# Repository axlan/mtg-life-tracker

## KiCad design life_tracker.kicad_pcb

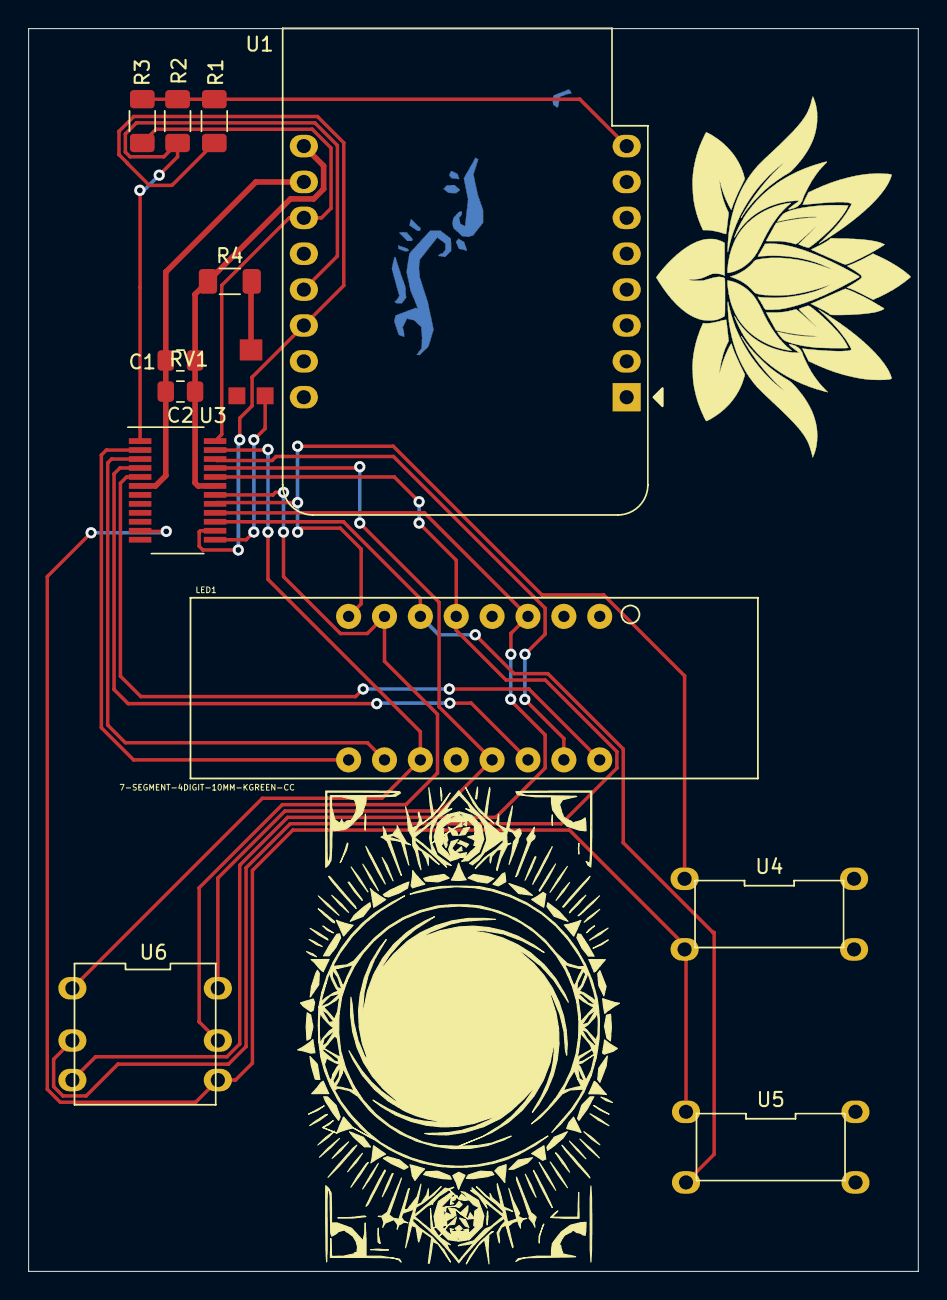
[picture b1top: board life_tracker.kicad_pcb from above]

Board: 2 copper layers, 63.0 x 88.0 mm, 16 parts (1 on the bottom side), 21 nets.

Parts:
C1: 10uF; C_0805_2012Metric_Pad1.18x1.45mm_HandSolder
C2: 0.1uF; C_0805_2012Metric_Pad1.18x1.45mm_HandSolder
LED1: 7-SEGMENT-4DIGIT-10MM-KGREEN-CC; 7-SEGMENT-4DIGIT-YOUNGSUN
R1, R2, R3, R4: 4.7k; R_1206_3216Metric_Pad1.30x1.75mm_HandSolder
RV1: 100k; TC33-SMD-Trimpot
U1: WeMos_D1_mini; WEMOS_D1_mini_light
U3: AS1115-BSST; QSOP-24_3.9x8.7mm_P0.635mm
U4, U5: PTS526-tactile-button; TACTILE-DIP-BUTTON
U6: TACTILE-NAV-STICK-DIP
svg2mod: G***; squirrel2
svg2mod#2: G***; lotus
svg2mod#3: G***; plains_walker_back_simp2

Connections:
+5V: C1.1, C2.1, R4.1, U1.9, U3.19
GND: C1.2, C2.2, U1.10, U3.6
unnamed: LED1.1, U3.2
unnamed: LED1.2, U3.3
unnamed: LED1.3, U3.23, U6.1
unnamed: LED1.5, U3.21, U6.6
unnamed: LED1.6, U3.4
unnamed: LED1.7, U3.22
unnamed: LED1.8, U3.5
unnamed: LED1.11, U3.16, U6.3
unnamed: LED1.13, U3.20, U6.2
unnamed: LED1.14, U3.15, U5.3
unnamed: LED1.15, U3.18, U6.5
unnamed: LED1.16, U3.17, U4.1
unnamed: R1.1, R2.1, R3.1, U1.8
unnamed: R1.2, U1.14, U3.14
unnamed: R2.2, U1.13, U3.1
unnamed: R3.2, U1.11, U3.24
unnamed: R4.2, RV1.2
unnamed: RV1.3, U3.13
unnamed: U3.11, U4.3, U5.1, U6.4

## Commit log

2021-10-16 initial test
2021-10-16 fix symbol directory
2021-10-16 remove unneeded file
2021-10-18 Initial pass at schematic.
2021-10-18 started routing PCB, need to flip D1
2021-10-20 Finished second revision.
2021-10-21 Add art.
2021-10-21 Moved resisters out from under d1.
2021-10-22 Added squirrel.
2021-10-23 Tiny correction to oled footprint.
2021-10-24 Added firmware project with main chip libraries.
2021-10-25 Added pygame demo for testing.
2021-10-25 Basic simulated counter.
2021-11-01 Added fork of as1115 for customization.
2021-11-02 Added the basic logic for buttons and 7seg display.
2021-11-04 Fix swapped I2C connection.
2021-11-04 Fixed key scan bugs.
2021-11-06 Add oled icons.
2021-11-07 Adding wifi
2021-11-07 Adding mqtt client.
2021-11-08 Add OTA, tracking totals with MQTT and plotting.
2021-11-16 Added art for second revision.
2021-11-16 Added footprints for new buttons and redid layout for bigger board, and OLED on top of D1.
2021-11-22 Fixed crash bug.
2021-11-22 Added dice roller mode.
2021-11-22 Fix displaying negative numbers.
2021-12-03 Change button priority and increase through hole size for buttons.
2021-12-10 Added snake game.
2021-12-10 Finish snake logic.
2021-12-10 Add menu
2021-12-28 Added WifiManager for settings control.
2021-12-28 Added settings menu.
2021-12-28 Added scrolling to settings.
2021-12-29 Fix plot script based on real data and update todos.
